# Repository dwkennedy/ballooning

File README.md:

# ballooning
all-in-one ballooning accessory (variometer, balloon cut-down, let down reel, tracking)

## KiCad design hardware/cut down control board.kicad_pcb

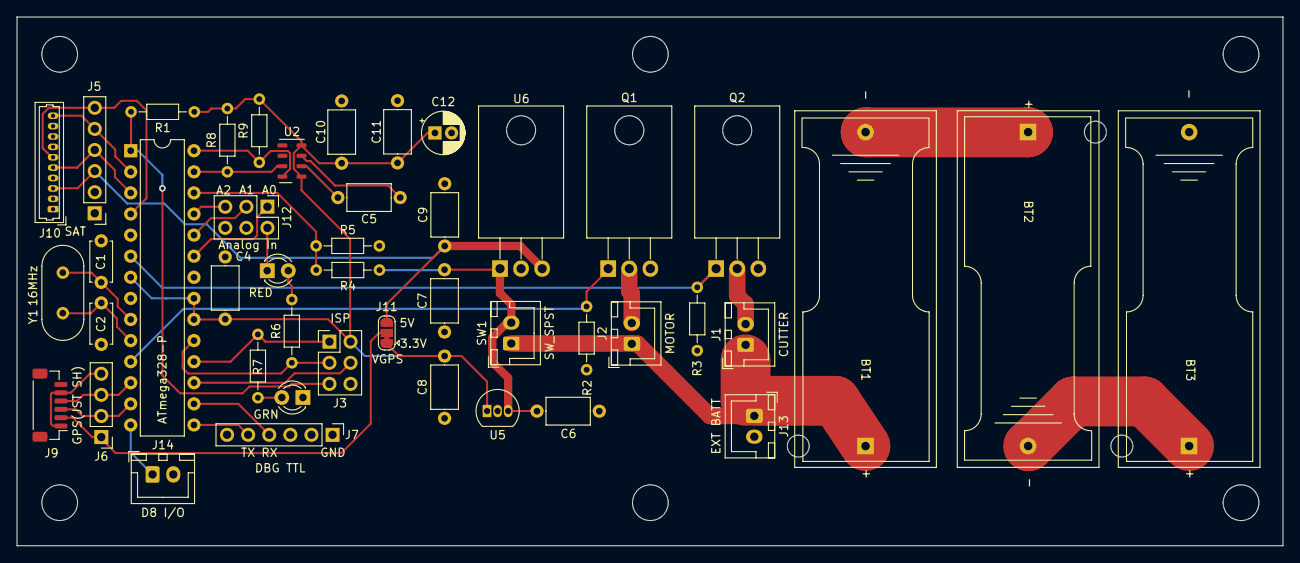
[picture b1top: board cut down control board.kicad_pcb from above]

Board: 2 copper layers, 152.4 x 63.7 mm, 45 parts (0 on the bottom side), 35 nets.

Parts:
BT1, BT2, BT3: Battery_Cell; BatteryHolder_Keystone_1051_1xCR123A
C1, C2: 22pF; C_Disc_D4.7mm_W2.5mm_P5.00mm
C4, C5, C10: 100nF; C_Axial_L5.1mm_D3.1mm_P7.50mm_Horizontal
C6, C7: 0.33uF; C_Axial_L5.1mm_D3.1mm_P7.50mm_Horizontal
C8, C9: 0.1uF; C_Axial_L5.1mm_D3.1mm_P7.50mm_Horizontal
C11: 1uF; C_Axial_L5.1mm_D3.1mm_P7.50mm_Horizontal
C12: 10uF; CP_Radial_D5.0mm_P2.00mm
D1: RED; LED_D3.0mm
D2: GRN; LED_D3.0mm
J1: CUTTER; JST_XH_B2B-XH-A_1x02_P2.50mm_Vertical
J2: MOTOR; JST_XH_B2B-XH-A_1x02_P2.50mm_Vertical
J3: ISP; PinHeader_2x03_P2.54mm_Vertical
J5: SAT(PIN HDR); PinHeader_1x06_P2.54mm_Vertical
J6: GPS(PIN HDR); PinHeader_1x04_P2.54mm_Vertical
J7: DBG TTL; PinHeader_1x06_P2.54mm_Vertical
J9: GPS(JST SH); JST_SH_BM06B-SRSS-TB_1x06-1MP_P1.00mm_Vertical
J10: SAT(10 picoblade); Molex_PicoBlade_53047-1010_1x10_P1.25mm_Vertical
J11: VGPS SELECT; SolderJumper-3_P1.3mm_Bridged12_RoundedPad1.0x1.5mm
J12: Analog In; PinHeader_2x03_P2.54mm_Vertical
J13: EXT BATT; JST_XH_B2B-XH-A_1x02_P2.50mm_Vertical
J14: D8 I/O; JST_XH_B2B-XH-A_1x02_P2.50mm_Vertical
Q1, Q2: FQP30N06L; TO-220-3_Horizontal_TabDown
R1, R2, R3: 10K; R_Axial_DIN0204_L3.6mm_D1.6mm_P7.62mm_Horizontal
R4: 100K; R_Axial_DIN0204_L3.6mm_D1.6mm_P7.62mm_Horizontal
R5: 33K; R_Axial_DIN0204_L3.6mm_D1.6mm_P7.62mm_Horizontal
R6, R7: 130; R_Axial_DIN0204_L3.6mm_D1.6mm_P7.62mm_Horizontal
R8, R9: 1K; R_Axial_DIN0204_L3.6mm_D1.6mm_P7.62mm_Horizontal
SW1: SW_SPST; JST_XH_B2B-XH-A_1x02_P2.50mm_Vertical
U1: ATmega328-P; DIP-28_W7.62mm
U2: MPL3115A2; NXP_LGA-8_3x5mm_P1.25mm_H1.1mm
U5: L78L33_TO92; TO-92_Inline
U6: L7805; TO-220-3_Horizontal_TabDown
Y1: 16MHz; Crystal_HC49-4H_Vertical

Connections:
+3.3V: C4.1, C8.2, C10.1, C11.1, C12.1, J3.2 (VCC), J11.1 (A), R1.1, R8.2, R9.2, U1.7 (VCC), U1.20 (AVCC), U1.21 (AREF), U2.1 (VDD), U2.4 (VDDIO), U5.1 (VO)
+5V: C9.2, J5.3, J10.3, J11.3 (B), U6.3 (OUT)
+9V: C6.2, C7.2, R4.1, SW1.2 (B), U5.3 (VI), U6.1 (IN)
/+VGPS: J6.1, J9.2, J11.2 (C)
/A0: J12.1, U1.23 (PC0)
/A1: J12.3, U1.24 (PC1)
/A2: J12.5, U1.25 (PC2)
/BATT_SENSE: R4.2, R5.1, U1.26 (PC3)
/CUTTER: Q2.1 (G), R3.1, U1.6 (PD4)
/LETDOWN_MOTOR: Q1.1 (G), R2.1, U1.11 (PD5)
/MISO: J3.1 (MISO), R7.1, U1.18 (PB4)
/MOSI: J3.4 (MOSI), U1.17 (PB3)
/RESET: J3.5 (~RST), R1.2, U1.1 (~RESET/PC6)
/RING: J5.6, J10.6, U1.4 (PD2)
/RX_DBG: J7.4, U1.16 (PB2)
/RX_GPS: J6.3, J9.4, U1.12 (PD6)
/RX_SAT: J5.5, J10.10, U1.2 (PD0)
/SCK: J3.3 (SCK), R6.1, U1.19 (PB5)
/SCL: R9.1, U1.28 (PC5), U2.8 (SCL)
/SDA: R8.1, U1.27 (PC4), U2.7 (SDL)
/TX_DBG: J7.5, U1.15 (PB1)
/TX_GPS: J6.2, J9.3, U1.13 (PD7)
/TX_SAT: J5.4, J10.5, U1.3 (PD1)
GND: BT3.2 (-), C1.2, C2.2, C4.2, C5.2, C6.1, C7.1, C8.1, C9.1, C10.2, C11.2, C12.2, D1.1 (K), D2.1 (K), J3.6 (GND), J5.1, J6.4, J7.1, J9.1, J9.5, J10.1, J12.2, J12.4, J12.6, J13.2, J14.2, Q1.3 (S), Q2.3 (S), R2.2, R3.2, R5.2, U1.8 (GND), U1.22 (GND), U2.3 (GND), U5.2 (GND), U6.2 (GND)
unnamed: BT1.2 (-), BT2.1 (+)
unnamed: BT2.2 (-), BT3.1 (+)
unnamed: C1.1, U1.9 (XTAL1/PB6), Y1.2
unnamed: C2.1, U1.10 (XTAL2/PB7), Y1.1
unnamed: C5.1, U2.2 (CAP)
unnamed: D1.2 (A), R6.2
unnamed: D2.2 (A), R7.2
unnamed: J1.2, Q2.2 (D)
unnamed: J2.2, Q1.2 (D)
unnamed: J14.1, U1.14 (PB0)
VDD: BT1.1 (+), J1.1, J2.1, J13.1, SW1.1 (A)

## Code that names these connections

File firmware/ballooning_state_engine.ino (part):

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#define MOTOR (2)

// hot-wire cutter port
#define CUTTER (3)

// GPS LED port
#define LED_GPS (12)

// battery voltage analog input
#define BATT_SENSE A3

// length of filter (N must be odd)
#define N (33)
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
// lines on rockblock labelled backwards; TX on RB is wired to TX on 328P
#define satSerial Serial
#define RING_PIN (8)
SoftwareSerial gpsSerial (10,9); // RX, TX
SoftwareSerial consoleSerial (7,6); // RX, TX 
IridiumSBD modem(satSerial, -1, RING_PIN);  // Declare the IridiumSBD object
TinyGPSPlus gps;  // Declare the TinyGPSPlus object

// vector of filter coefficients
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  // configure control ports and make sure they're off
  pinMode(MOTOR, OUTPUT);  // motor control port
  digitalWrite(MOTOR, LOW);  // motor off
  pinMode(CUTTER, OUTPUT);  // cutter control port
  digitalWrite(CUTTER, LOW);  // cutter off

  // set up GPS LED
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  digitalWrite(LED_BUILTIN, LOW);

  // iridium modem ring signal
  pinMode(RING_PIN, INPUT);

#ifdef MPR
  // pressure sensor reset
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  // when it's update time or there is a message waiting for RX, build the TX status message : 
  // example message: *** SDB TX: 000B21107916E8B8192A07531FA6E1B99101D7E100000 size 31

  if ( (!digitalRead(RING_PIN))
        || (modem.getWaitingMessageCount() > 0)
        || (config.update_interval_satellite && (this_update_millis < last_update_millis))) {
    #ifdef DEBUG
    if (!digitalRead(RING_PIN)) {
        consoleSerial.println(F("*** SDB RING"));
    }
    #endif
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    consoleSerial.print(F(","));
    consoleSerial.print(active_state);
    consoleSerial.print(F(","));
    //consoleSerial.print(digitalRead(RING_PIN)?"IDLE,":"RING,");
    /*int c = gps.time.minute();
    if (c < 10) {
      consoleSerial.print(F("0")); // leading zero
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
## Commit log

2018-12-29 Add files via upload
    Arduino implementation of FIR slope filter with MS5611 pressure sensor
2022-08-18 Add files via upload
    code for let down reel/ cut down device using BMP180 pressure sensor
2022-08-18 Add files via upload
    sketch of circuit
2022-08-25 Add files via upload
    added a bunch of stuff, serial commands, gps, fleshed out states
2022-08-25 Add files via upload
    added leading zeros on gps minute/second in periodic update string
2022-08-30 Add files via upload
    fix to status message update interval
2022-08-30 Add files via upload
    added haversine function to compute distance between two lat/lons
2022-08-31 Add files via upload
    added some links to special libraries used and board manager URL for bare atmega328p
    http://www.bamfordresearch.com/files/package_jb23_insystemmcu_index.json
2022-08-31 Add files via upload
    add gps update code and calculation of distance over surface of earth from launch to balloon
    add gps LED code (blink LED_GPS port if a lock; off=no lock)
2022-08-31 Add files via upload
    fixed bug in haversine testing code (constant with leading zero interpreted as octal by compiler)
    fixed some other minor bugs
    removed debugging code
2022-08-31 Add files via upload
    made "letdown" command update the launch location to latest gps location, if the gps solution is valid
    "letdown" could also be "launch" command to simulate a launch, since they do the same things
2022-09-01 Add files via upload
    added code for Honeywell MPR pressure sensor
    improved timing for pressure sensor sampling
2022-09-04 Add files via upload
    wired DO 8 to reset pin on MPR pressure sensor
    defined RESET_PIN in code to reset the sensor on boot
    modified adafruit MPR library to use only integer math and return integer value of pressure in Pa
2022-09-04 Add files via upload
    modified adafruit MPR library to read pressure and convert to Pa using only integer math
2022-09-04 Add files via upload
    setting update interval to zero disables the update
    fix up the debug code to use #ifdef
2022-09-04 Add files via upload
    (n-1) % N can produce -1 if n is an int so I made n a uint16_t. n is the index into the circular buffer of samples so 0<= n < N, i.e. n= 0..(N-1)
2022-09-04 Add files via upload
    add delay to avoid double blink/reset on power on
2022-09-04 Add files via upload
    refactor code
2022-09-04 Add files via upload
    LED flash when pressure is missing/invalid
2022-09-16 Add files via upload
    adding receipt/parsing of commands via satellite, clear mobile originated buffer after transmit attempt
2022-09-18 Add files via upload
    add configuration and other command via 2nd serial port on boot
2022-09-18 Add files via upload
    script to send configuration commands to device on power up
2022-09-20 Add files via upload
    added MPL3115A2 sensor support
    rockblock RING ping support
    fixed course/speed scaling (100ths of degrees and 100ths of knots)
    initialized MT_buffer_size correctly before SBD tx/rx
    analog input 3 monitors battery voltage. 4:1 voltage divider (range=3.3*4 = 13.2)
2022-09-23 reorganized files into directories
2022-09-23 move additional files
    solidworks, etc
2022-09-23 added more solidworks files
2022-09-23 added kicad project
2022-09-23 correct typo
2022-09-23 another typo
2022-09-23 testing github change
2022-09-25 added footprints
2022-09-27 update pcb layout
2022-09-27 More updates to PCB
2022-09-29 board layout
2022-09-30 changed footprint J2
2022-10-12 finished board, generated gerbers
2022-10-12 Added graphics, D8 input, and external power connector
2022-10-13 final board 10/12/2022
2022-10-13 update BOM
2022-10-14 annotated BOM with Mouser links
2022-10-15 flipped motor down
2022-10-16 updates to enclosure and mechanism
2022-10-17 added mockup of rockblock and ultimate gps board
2022-10-17 add detail to GPS and Sat modem model
2022-10-17 customized tube caps
2022-10-17 added switch and switch housing, longer quick-release pin
2022-10-17 backups
2022-10-18 phoenix connector QD terminal block
2022-10-19 reworked top of enclosure
2022-10-20 make spool STL and gcode
2022-10-21 create rigging pog
2022-10-21 UPDATE .gitignore to ignore solidworks temporary files
2022-10-24 added short parachute monofilament pigtail and loop in long balloon pigtail
2022-10-24 add monofilament rigging back
2022-10-24 embiggened holes, adjusted clearances on spool bushing
2022-10-24 3d printing files updated
2022-10-24 redo changes
2022-10-24 redo some changes
2022-10-24 fix to master assembly mate
2022-10-24 added molex picoblade datasheets
2022-10-25 reversed picoblade connector for rockblock 9603
    cable pin 1 to pin 10, pin 2 to 9, etc (premade cables are reversed)
2022-10-25 update gerbers and drill files
2022-10-25 set SLEEP_PIN for rockblock to HIGH (should be awake)
2022-10-26 firmware bugfix
2022-10-26 add timed launch feature
2022-10-27 add hex output for Rockblock message
2022-10-27 remove old command interpreter functions
2022-10-27 swapped gps rx/tx pins, modified blinks, compute voltage
2022-10-27 debug code for satellite RING
2022-10-28 explicitly select external analog reference voltage; improve serial debug output
2022-10-28 added CFG, PNG commands
2022-10-28 fix letdown_delay bug
    device was waiting letdown_delay seconds before "launching" then waiting another letdown_delay seconds before activating letdown motor.
2022-10-28 add debug messages to CFG and PNG command handlers
2022-10-28 updates
    bug fix for firmware, comparison between uint32 and int32 (typecast)
    flip rockblock 9603, longer screws, longer spacers
    new rigging pog
2022-10-28 add hot wire cutter assembly holder
2022-10-28 new top enclosure brace w/ hot wire cutter assembly mount
2022-10-28 remove rockblock sleep from schematic and pcb
2022-10-28 modify receiver plates
2022-10-29 set materials and appearances
2022-10-29 shorten motor test to 50ms
2022-10-29 add foam spacer to bottom
2022-10-29 tweak the top enclosure brace hot wire cutter holder
2022-10-29 check for swapped min/max lat and lon, correct automagically
2022-10-30 fix ADC formula to get voltage
2022-10-30 add PDF of pcb and schematic as produced
2022-10-30 trimmed lloyd noble test geofence
2022-10-30 added decode function and more verbose output for programming device
2022-10-30 make dump_config function, search for CFG in device output
2022-10-30 redo western boundary at Lloyd Noble so we don't have to walk
2022-10-30 LED pin name fixes, gps validity check attempt to fix, LED now interrupt driven
2022-10-31 move turn-on of interrupt driven blink to end of setup
2022-10-31 update switch housing on bottom enclosure brace
2022-10-31 fixed two bugs
    firmware: gps light stays on steady when valid & recent
    configure.py: convert hex ascii bytes to python bytes
2022-10-31 read the BAD cfg after programming and print in readable form
2022-10-31 improve switch holder on enclosure brace bottom
2022-11-01 added mike's test configuration
2022-11-02 Fix mike config to let down after power on
2022-11-03 added checkcfg to dump the current configuration
2022-11-03 update top enclosure brace to smiley face
2022-11-03 init pressure sensor before sat modem
2022-11-03 fix typo
2022-11-03 add wire lengths in schematic
2022-11-03 added top enclosure brace artwork
2022-11-03 fix CFG bug
    CFG memcpy was in wrong direction, so corrupted config structure
    need to copy FROM config, TO MO_buffer
    tested and works now
2022-11-03 check Iridium status and don't process received message unless successful (status 0)
2022-11-04 improve hot wire cutter holder
2022-11-05 Update smiley face
2022-11-05 strip cr/lf to compress output
2022-11-05 update all STL files
2022-11-07 tweak enclosure top
2022-11-07 update top enclosure brace STL file
2022-11-07 submit configuration to database server
2022-11-07 make device report IMEI on boot (in DEBUG mode)
2022-11-07 tweak top brace
2022-11-07 move cutter back inside device
2022-11-09 monkey with top brace and delete old files
2022-11-09 update manual
2022-11-10 check battery voltage before self-test
2022-11-10 clarify config update source (PC is now SERIAL)
2022-11-11 fix CFG bug in firmware (responded to malformed, overlength packets)
2022-11-11 fix let-down command and update configure.py to work around CFG buffer bug
2022-11-12 rename spool -> spool axle to differentiate from spool flange
2022-11-13 put serialnumber and imei in every if(x) configuration
2022-11-14 added code to change after CFG fix applied to all devices
2022-11-16 cut debugging messages
    added cutXX and letXX commands, fixed some if/then/else logic in process_cmd, moved some stuff into process_cmd that was in main loop(), changed default unprogrammed config, added debug message for v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
2022-11-16 first pass
2022-11-16 added additional states for cause of cut-down (manual, time, pressure, geofence, dist)
2022-11-17 refactor code
2022-11-17 LET command in serial setup mode fix
2022-11-17 redo satellite communication message handling & fix boot up motor/cutter test
2022-11-19 modem timing adjustments
2022-11-24 motor stall detect added + refactor code
2022-11-24 make unit_id # of gps satellites tracked
2022-11-24 output IMEI after serial command mode
2022-11-24 update for new firmware *CFG and *IMEI messages
2022-11-24 added hdop*10 (uint8_t) and changes satellites to uint8_t
2022-11-24 add sos flash function; satellite and hdop to debugging
2022-11-26 add CRC16 to CFG and beacons, update server to match
2022-11-26 add comments and increase verbosity
2022-11-26 adjust sos_flash logic
2022-11-26 tweak battery/circuit test sequence
2022-11-26 add sos flash to indicate pressure sensor error
2022-11-26 initial CHANGELOG.md
2022-11-26 added rigging bulkhead assembly
2022-11-26 adjust dimensions of foam slot
2022-11-27 created STL files
2022-11-27 create bulkhead prusa project
2022-11-28 tweak nut dimensions
2022-11-28 add small bottom bulkhead for letdown line
2022-11-28 dimension tweaks and new STL
2022-11-29 more tweaks to small bulkhead
2023-01-06 embiggen spool
2023-01-09 add reinforcement ridge to edge of spool
2023-01-17 large spool tweak
2023-01-17 bumped motor voltage drop threshold for detection
2023-01-19 spool axle; more clearance between plates
2023-01-19 add install/compile tips
2023-01-19 loosen threshold for overcurrent
